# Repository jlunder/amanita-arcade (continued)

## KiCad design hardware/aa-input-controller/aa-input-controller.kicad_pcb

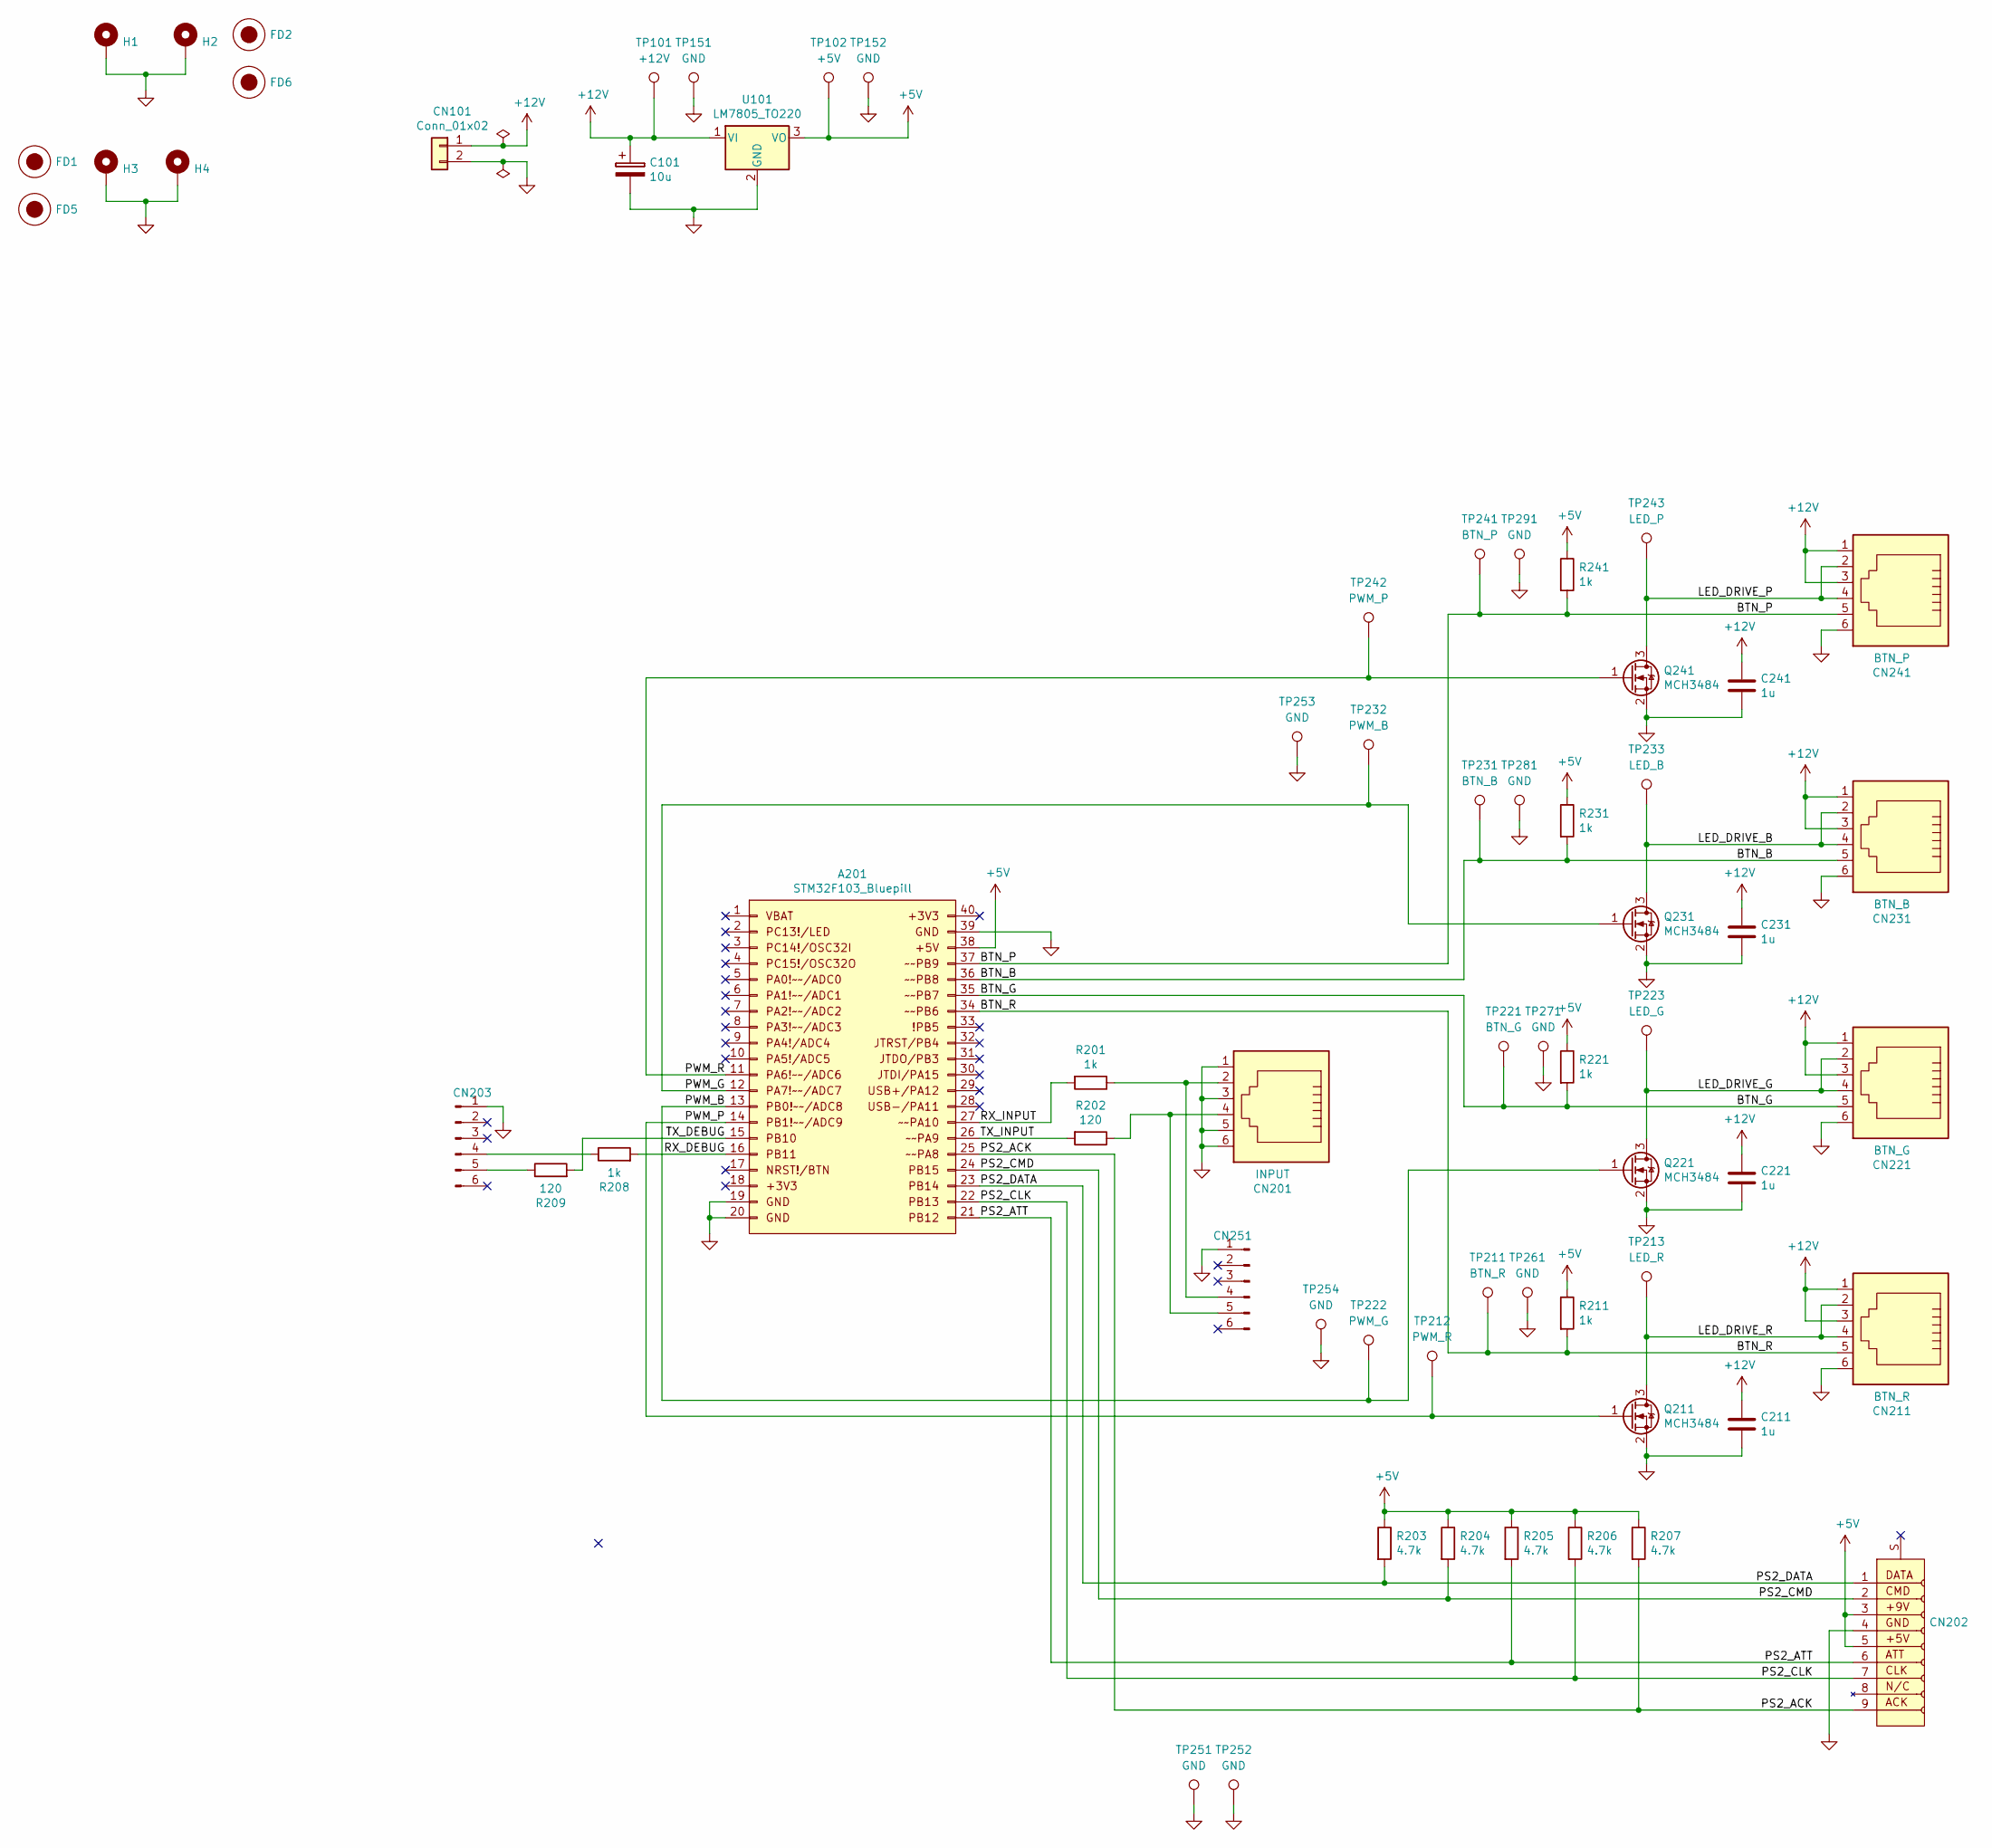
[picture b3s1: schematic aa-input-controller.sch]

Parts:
A201: STM32F103_Bluepill; Maple_Mini
C101: 10u; CP_Radial_D10.0mm_P2.50mm_P5.00mm
C211, C221, C231, C241: 1u; C_0805_2012Metric
CN101: Conn_01x02; SolderWirePad_1x02_P5.08mm_Drill1.5mm
CN201: INPUT; 6P6C_Assmann_A-2014-1-4
CN202: Connector_Sony_Playstation_DualShock_Female; Connector_SonyPS2DualShock_Female
CN203, CN251: Conn_01x06_Male; PinHeader_1x06_P2.54mm_Vertical
CN211: BTN_R; 6P6C_Assmann_A-2014-1-4
CN221: BTN_G; 6P6C_Assmann_A-2014-1-4
CN231: BTN_B; 6P6C_Assmann_A-2014-1-4
CN241: BTN_P; 6P6C_Assmann_A-2014-1-4
FD1, FD2: Fiducial; Fiducial_1mm_Dia_2.54mm_Outer_CopperTop
FD5, FD6: Fiducial; StencilAlignment_1.27mm
H1, H2, H3, H4: MountingHole_Pad; MountingHole_2.7mm_M2.5_Pad_Via
Q211, Q221, Q231, Q241: MCH3484; SOT-323_SC-70
R201, R208, R211, R221, R231, R241: 1k; R_0603_1608Metric
R202, R209: 120; R_0603_1608Metric
R203, R204, R205, R206, R207: 4.7k; R_0603_1608Metric
TP101: +12V; TestPoint_Loop_D1.80mm_Drill1.0mm_Beaded
TP102: +5V; TestPoint_Loop_D1.80mm_Drill1.0mm_Beaded
TP151, TP152, TP251, TP252, TP253, TP254, TP261, TP271, TP281, TP291: GND; TestPoint_Loop_D1.80mm_Drill1.0mm_Beaded
TP211: BTN_R; TestPoint_Loop_D1.80mm_Drill1.0mm_Beaded
TP212: PWM_R; TestPoint_Loop_D1.80mm_Drill1.0mm_Beaded
TP213: LED_R; TestPoint_Loop_D1.80mm_Drill1.0mm_Beaded
TP221: BTN_G; TestPoint_Loop_D1.80mm_Drill1.0mm_Beaded
TP222: PWM_G; TestPoint_Loop_D1.80mm_Drill1.0mm_Beaded
TP223: LED_G; TestPoint_Loop_D1.80mm_Drill1.0mm_Beaded
TP231: BTN_B; TestPoint_Loop_D1.80mm_Drill1.0mm_Beaded
TP232: PWM_B; TestPoint_Loop_D1.80mm_Drill1.0mm_Beaded
TP233: LED_B; TestPoint_Loop_D1.80mm_Drill1.0mm_Beaded
TP241: BTN_P; TestPoint_Loop_D1.80mm_Drill1.0mm_Beaded
TP242: PWM_P; TestPoint_Loop_D1.80mm_Drill1.0mm_Beaded
TP243: LED_P; TestPoint_Loop_D1.80mm_Drill1.0mm_Beaded
U101: LM7805_TO220; TO-220-3_Horizontal_TabDown

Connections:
+5V: A201.38, CN202.3, CN202.5, R203.1, R204.1, R205.1, R206.1, R207.1, R211.1, R221.1, R231.1, R241.1, TP102.1, U101.3 (VO)
+12V: C101.1, C211.1, C221.1, C231.1, C241.1, CN101.1, CN211.1, CN211.3, CN221.1, CN221.3, CN231.1, CN231.3, CN241.1, CN241.3, TP101.1, U101.1 (VI)
/BTN_B: A201.36, CN231.5, R231.2, TP231.1
/BTN_G: A201.35, CN221.5, R221.2, TP221.1
/BTN_P: A201.37, CN241.5, R241.2, TP241.1
/BTN_R: A201.34, CN211.5, R211.2, TP211.1
/LED_DRIVE_B: CN231.2, CN231.4, Q231.3 (D), TP233.1
/LED_DRIVE_G: CN221.2, CN221.4, Q221.3 (D), TP223.1
/LED_DRIVE_P: CN241.2, CN241.4, Q241.3 (D), TP243.1
/LED_DRIVE_R: CN211.2, CN211.4, Q211.3 (D), TP213.1
/PS2_ACK: A201.25, CN202.9, R207.2
/PS2_ATT: A201.21, CN202.6, R205.2
/PS2_CLK: A201.22, CN202.7, R206.2
/PS2_CMD: A201.24, CN202.2, R204.2
/PS2_DATA: A201.23, CN202.1, R203.2
/PWM_B: A201.13, Q221.1 (G), TP222.1
/PWM_G: A201.12, Q231.1 (G), TP232.1
/PWM_P: A201.14, Q211.1 (G), TP212.1
/PWM_R: A201.11, Q241.1 (G), TP242.1
/RX_DEBUG: A201.16, R208.2
/RX_INPUT: A201.27, R201.2
/TX_DEBUG: A201.15, R209.2
/TX_INPUT: A201.26, R202.2
GND: A201.19, A201.20, A201.39, C101.2, C211.2, C221.2, C231.2, C241.2, CN101.2, CN201.1, CN201.3, CN201.5, CN201.6, CN202.4, CN203.1, CN211.6, CN221.6, CN231.6, CN241.6, CN251.1, H1.1, H2.1, H3.1, H4.1, Q211.2 (S), Q221.2 (S), Q231.2 (S), Q241.2 (S), TP151.1, TP152.1, TP251.1, TP252.1, TP253.1, TP254.1, TP261.1, TP271.1, TP281.1, TP291.1, U101.2 (GND)
unnamed: CN201.2, CN251.4, R201.1
unnamed: CN201.4, CN251.5, R202.1
unnamed: CN203.4, R208.1
unnamed: CN203.5, R209.1

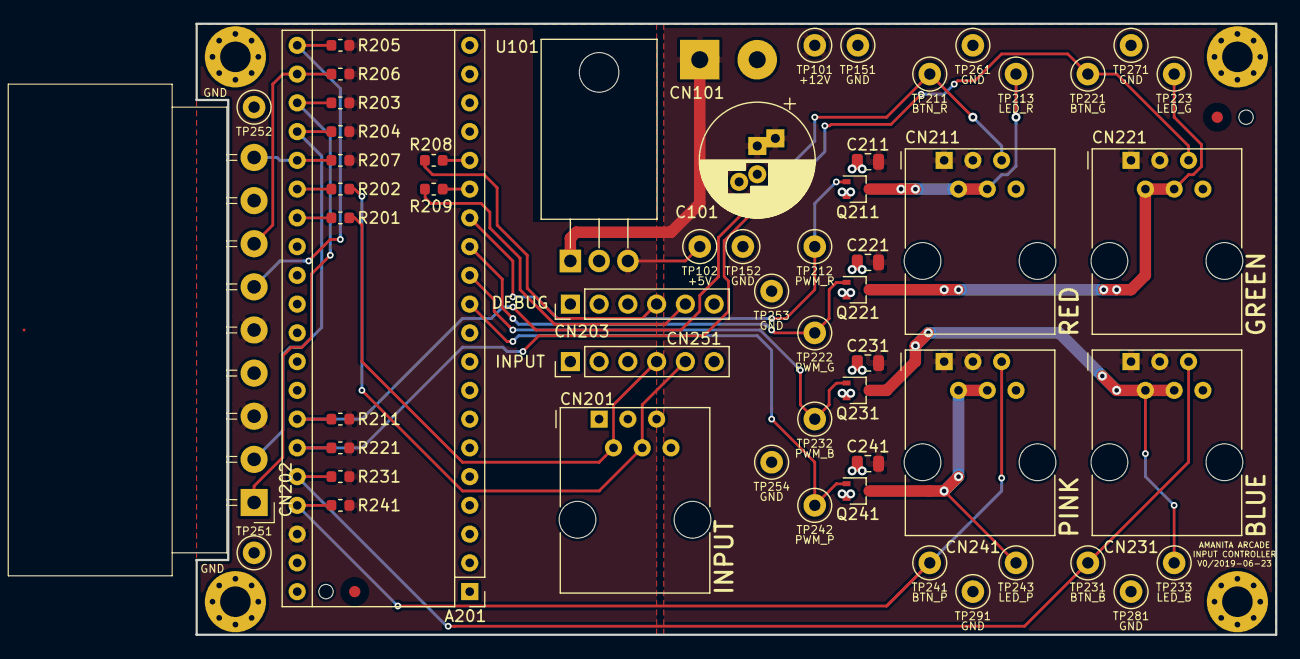
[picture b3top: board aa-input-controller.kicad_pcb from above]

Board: 2 copper layers, 95.4 x 54.0 mm, 65 parts (0 on the bottom side), 28 nets.

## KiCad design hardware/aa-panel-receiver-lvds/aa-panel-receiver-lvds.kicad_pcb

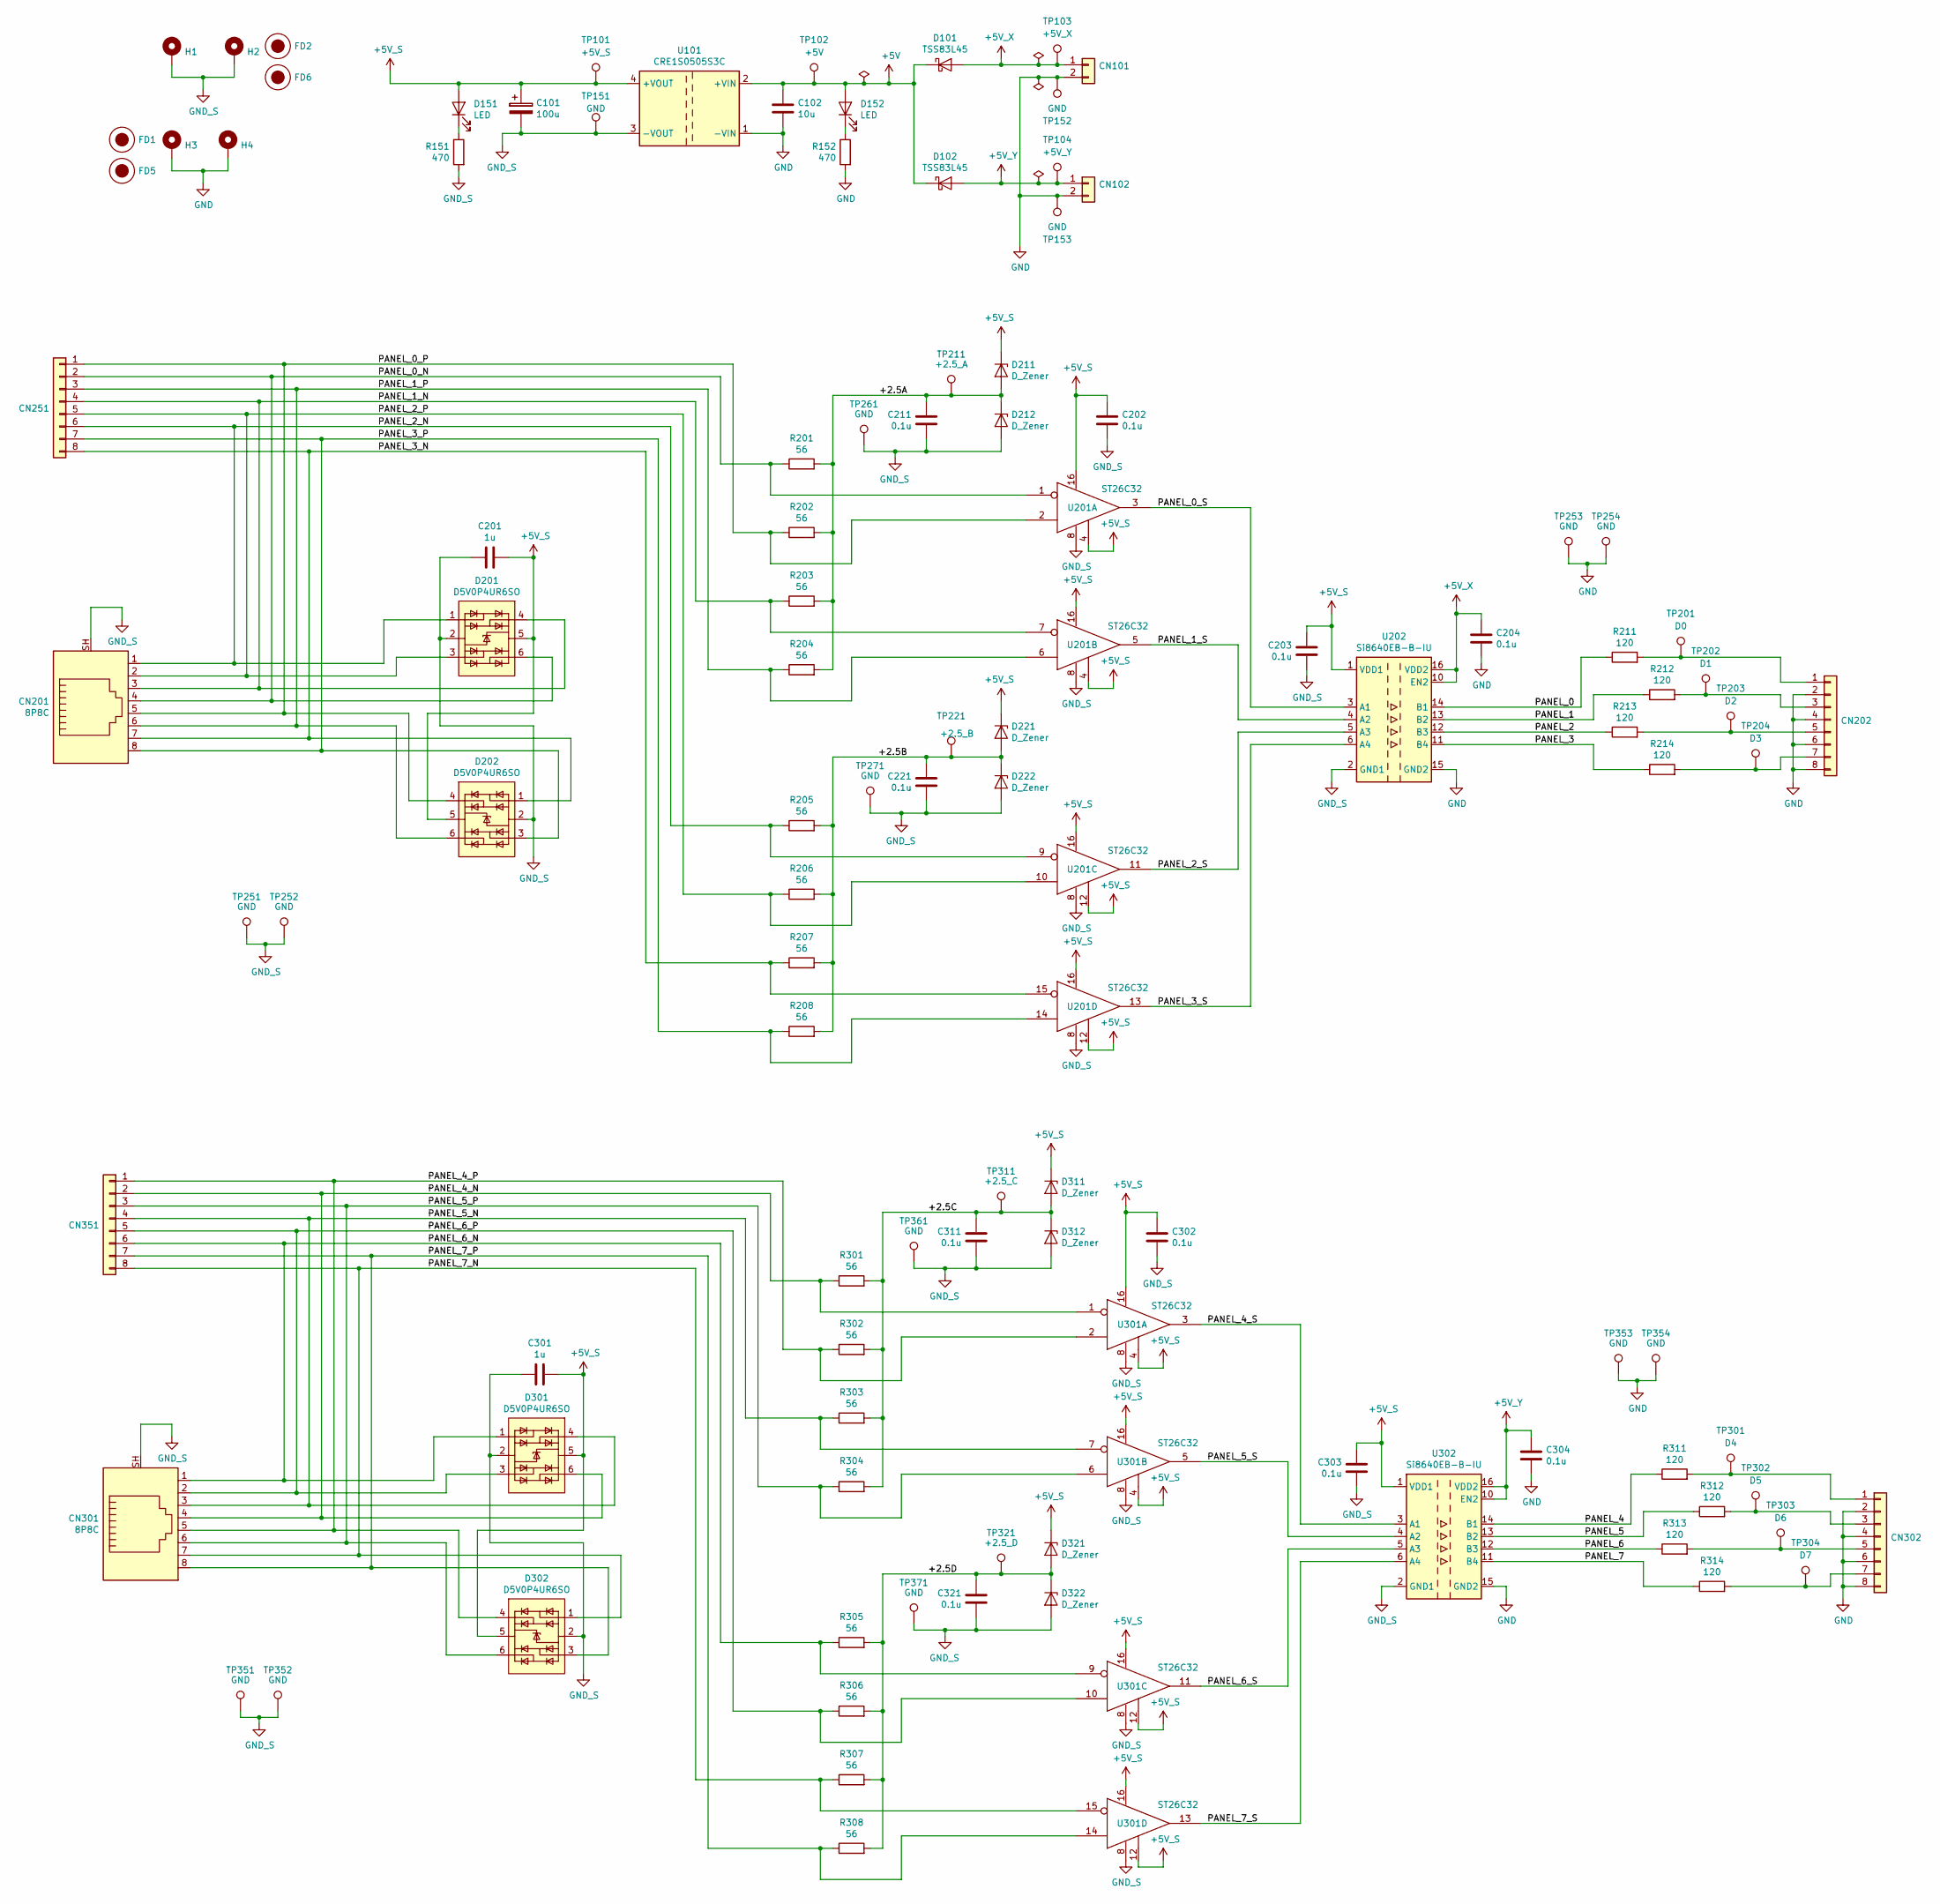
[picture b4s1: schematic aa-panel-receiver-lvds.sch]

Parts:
C101: 100u; CP_Radial_D10.0mm_P2.50mm_P5.00mm
C102: 10u; CP_Radial_D6.3mm_P2.50mm
C201, C301: 1u; C_0805_2012Metric
C202, C203, C204, C211, C221, C302, C303, C304, C311, C321: 0.1u; C_0603_1608Metric
CN101, CN102: Conn_01x02; SolderWirePad_1x02_P5.08mm_Drill1.5mm
CN201, CN301: 8P8C; 8P8C_Assmann_A-2014-2S-4
CN202, CN251, CN302, CN351: Conn_01x08; PinHeader_2x04_P2.54mm_Vertical
D101, D102: TSS83L45; D_SOD-128
D151, D152: LED; LED_0603_1608Metric
D201, D202, D301, D302: D5V0P4UR6SO; SOT-23-6
D211, D212, D221, D222, D311, D312, D321, D322: D_Zener; D_DO-35_SOD27_P2.54mm_Vertical_KathodeUp
FD1, FD2: Fiducial; Fiducial_1mm_Dia_2.54mm_Outer_CopperTop
FD5, FD6: Fiducial; StencilAlignment_1.27mm
H1, H2, H3, H4: MountingHole_Pad; MountingHole_2.7mm_M2.5_Pad_Via
R151, R152: 470; R_0603_1608Metric
R201, R202, R203, R204, R205, R206, R207, R208, R301, R302, R303, R304, R305, R306, R307, R308: 56; R_0603_1608Metric
R211, R212, R213, R214, R311, R312, R313, R314: 120; R_0603_1608Metric
TP101: +5V_S; TestPoint_Loop_D1.80mm_Drill1.0mm_Beaded
TP102: +5V; TestPoint_Loop_D1.80mm_Drill1.0mm_Beaded
TP103: +5V_X; TestPoint_Loop_D1.80mm_Drill1.0mm_Beaded
TP104: +5V_Y; TestPoint_Loop_D1.80mm_Drill1.0mm_Beaded
TP151, TP152, TP153, TP251, TP252, TP253, TP254, TP261, TP271, TP351, TP352, TP353, TP354, TP361, TP371: GND; TestPoint_Loop_D1.80mm_Drill1.0mm_Beaded
TP201: D0; TestPoint_Loop_D1.80mm_Drill1.0mm_Beaded
TP202: D1; TestPoint_Loop_D1.80mm_Drill1.0mm_Beaded
TP203: D2; TestPoint_Loop_D1.80mm_Drill1.0mm_Beaded
TP204: D3; TestPoint_Loop_D1.80mm_Drill1.0mm_Beaded
TP211: +2.5_A; TestPoint_Loop_D1.80mm_Drill1.0mm_Beaded
TP221: +2.5_B; TestPoint_Loop_D1.80mm_Drill1.0mm_Beaded
TP301: D4; TestPoint_Loop_D1.80mm_Drill1.0mm_Beaded
TP302: D5; TestPoint_Loop_D1.80mm_Drill1.0mm_Beaded
TP303: D6; TestPoint_Loop_D1.80mm_Drill1.0mm_Beaded
TP304: D7; TestPoint_Loop_D1.80mm_Drill1.0mm_Beaded
TP311: +2.5_C; TestPoint_Loop_D1.80mm_Drill1.0mm_Beaded
TP321: +2.5_D; TestPoint_Loop_D1.80mm_Drill1.0mm_Beaded
U101: CRE1S0505S3C; Converter_DCDC_muRata_CRE1xxxxxx3C_THT
U201, U301: ST26C32; SOIC-16_3.9x9.9mm_P1.27mm
U202, U302: Si8640EB-B-IU; QSOP-16_3.9x4.9mm_P0.635mm

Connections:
+5V: C102.1, D101.1 (K), D102.1 (K), D152.2 (A), TP102.1, U101.2 (+VIN)
+5V_S: C101.1, C201.1, C202.1, C203.1, C301.1, C302.1, C303.1, D151.2 (A), D201.5 (K), D202.5 (K), D211.1 (K), D221.1 (K), D301.5 (K), D302.5 (K), D311.1 (K), D321.1 (K), TP101.1, U101.4 (+VOUT), U201.4 (ENABLE), U201.12 (ENABLE), U201.16 (VCC), U202.1 (VDD1), U301.4 (ENABLE), U301.12 (ENABLE), U301.16 (VCC), U302.1 (VDD1)
+5V_X: C204.1, CN101.1, D101.2 (A), TP103.1, U202.10 (EN2), U202.16 (VDD2)
+5V_Y: C304.1, CN102.1, D102.2 (A), TP104.1, U302.10 (EN2), U302.16 (VDD2)
/+2.5A: C211.1, D211.2 (A), D212.1 (K), R201.2, R202.2, R203.2, R204.2, TP211.1
/+2.5B: C221.1, D221.2 (A), D222.1 (K), R205.2, R206.2, R207.2, R208.2, TP221.1
/+2.5C: C311.1, D311.2 (A), D312.1 (K), R301.2, R302.2, R303.2, R304.2, TP311.1
/+2.5D: C321.1, D321.2 (A), D322.1 (K), R305.2, R306.2, R307.2, R308.2, TP321.1
/PANEL_0: R211.1, U202.14 (B1)
/PANEL_0_N: CN201.4, CN251.2, D201.6 (K), R201.1, U201.1 (E-)
/PANEL_0_P: CN201.5, CN251.1, D202.4 (K), R202.1, U201.2 (E+)
/PANEL_0_S: U201.3 (OUT), U202.3 (A1)
/PANEL_1: R212.1, U202.13 (B2)
/PANEL_1_N: CN201.3, CN251.4, D201.4 (K), R203.1, U201.7 (E-)
/PANEL_1_P: CN201.6, CN251.3, D202.6 (K), R204.1, U201.6 (E+)
/PANEL_1_S: U201.5 (OUT), U202.4 (A2)
/PANEL_2: R213.1, U202.12 (B3)
/PANEL_2_N: CN201.1, CN251.6, D201.1 (K), R205.1, U201.9 (E-)
/PANEL_2_P: CN201.2, CN251.5, D201.3 (K), R206.1, U201.10 (E+)
/PANEL_2_S: U201.11 (OUT), U202.5 (A3)
/PANEL_3: R214.1, U202.11 (B4)
/PANEL_3_N: CN201.7, CN251.8, D202.1 (K), R207.1, U201.15 (E-)
/PANEL_3_P: CN201.8, CN251.7, D202.3 (K), R208.1, U201.14 (E+)
/PANEL_3_S: U201.13 (OUT), U202.6 (A4)
/PANEL_4: R311.1, U302.14 (B1)
/PANEL_4_N: CN301.4, CN351.2, D301.6 (K), R301.1, U301.1 (E-)
/PANEL_4_P: CN301.5, CN351.1, D302.4 (K), R302.1, U301.2 (E+)
/PANEL_4_S: U301.3 (OUT), U302.3 (A1)
/PANEL_5: R312.1, U302.13 (B2)
/PANEL_5_N: CN301.3, CN351.4, D301.4 (K), R303.1, U301.7 (E-)
/PANEL_5_P: CN301.6, CN351.3, D302.6 (K), R304.1, U301.6 (E+)
/PANEL_5_S: U301.5 (OUT), U302.4 (A2)
/PANEL_6: R313.1, U302.12 (B3)
/PANEL_6_N: CN301.1, CN351.6, D301.1 (K), R305.1, U301.9 (E-)
/PANEL_6_P: CN301.2, CN351.5, D301.3 (K), R306.1, U301.10 (E+)
/PANEL_6_S: U301.11 (OUT), U302.5 (A3)
/PANEL_7: R314.1, U302.11 (B4)
/PANEL_7_N: CN301.7, CN351.8, D302.1 (K), R307.1, U301.15 (E-)
/PANEL_7_P: CN301.8, CN351.7, D302.3 (K), R308.1, U301.14 (E+)
/PANEL_7_S: U301.13 (OUT), U302.6 (A4)
GND: C102.2, C204.2, C304.2, CN101.2, CN102.2, CN202.2, CN202.4, CN202.6, CN202.8, CN302.2, CN302.4, CN302.6, CN302.8, H3.1, H4.1, R152.2, TP152.1, TP153.1, TP253.1, TP254.1, TP353.1, TP354.1, U101.1 (-VIN), U202.9 (GND2), U202.15 (GND2), U302.9 (GND2), U302.15 (GND2)
GND_S: C101.2, C201.2, C202.2, C203.2, C211.2, C221.2, C301.2, C302.2, C303.2, C311.2, C321.2, CN201.SH, CN301.SH, D201.2 (A), D202.2 (A), D212.2 (A), D222.2 (A), D301.2 (A), D302.2 (A), D312.2 (A), D322.2 (A), H1.1, H2.1, R151.2, TP151.1, TP251.1, TP252.1, TP261.1, TP271.1, TP351.1, TP352.1, TP361.1, TP371.1, U101.3 (-VOUT), U201.8 (GND), U202.2 (GND1), U202.8 (GND1), U301.8 (GND), U302.2 (GND1), U302.8 (GND1)
unnamed: CN202.1, R211.2, TP201.1
unnamed: CN202.3, R212.2, TP202.1
unnamed: CN202.5, R213.2, TP203.1
unnamed: CN202.7, R214.2, TP204.1
unnamed: CN302.1, R311.2, TP301.1
unnamed: CN302.3, R312.2, TP302.1
unnamed: CN302.5, R313.2, TP303.1
unnamed: CN302.7, R314.2, TP304.1
unnamed: D151.1 (K), R151.1
unnamed: D152.1 (K), R152.1

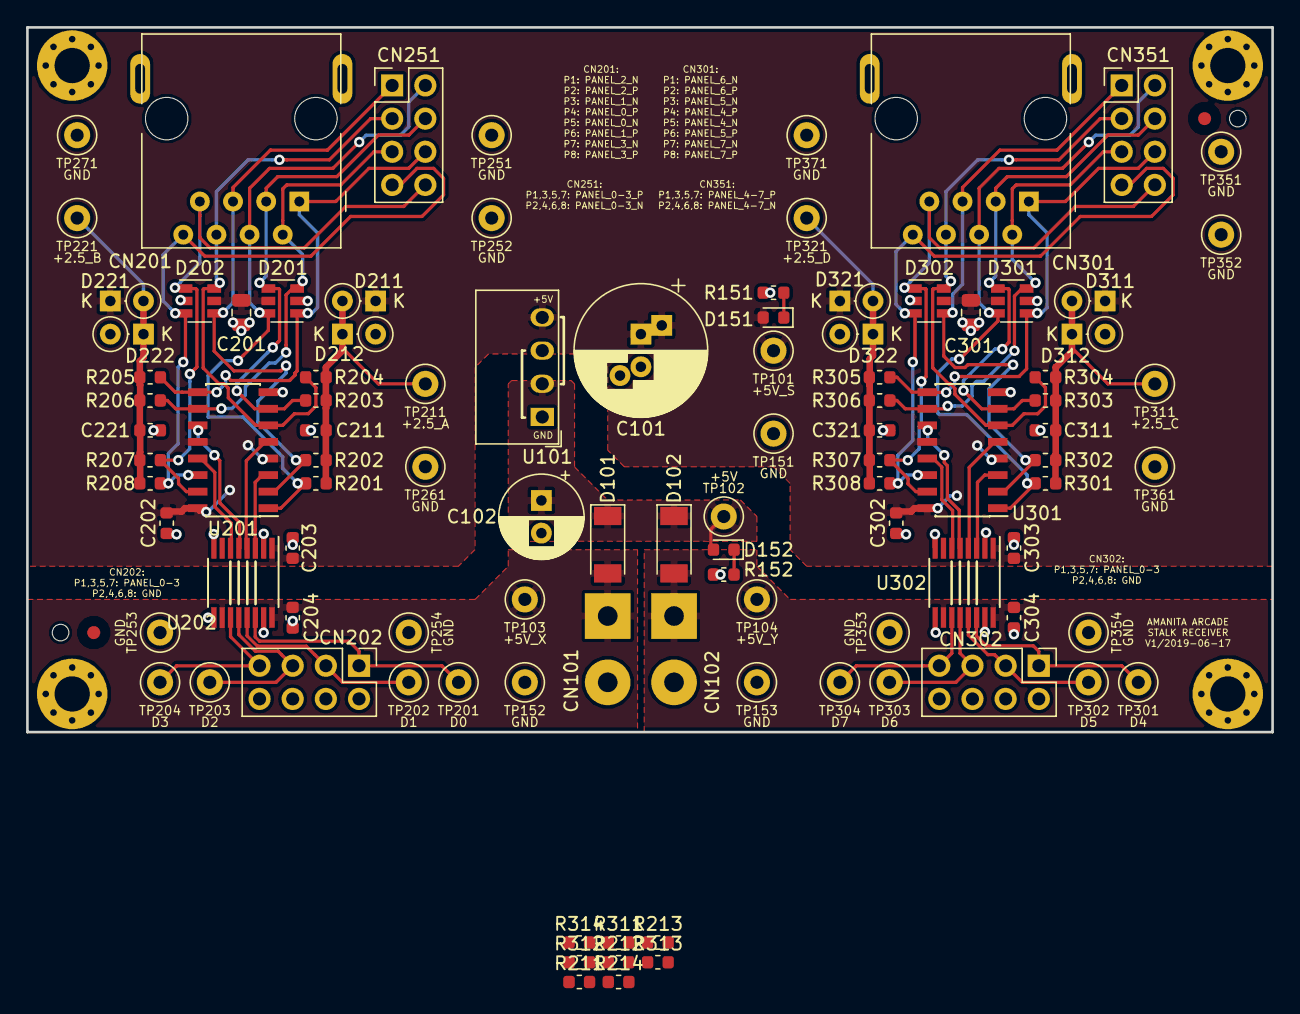
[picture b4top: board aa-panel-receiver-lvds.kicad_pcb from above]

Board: 2 copper layers, 95.4 x 54.0 mm, 108 parts (0 on the bottom side), 52 nets.

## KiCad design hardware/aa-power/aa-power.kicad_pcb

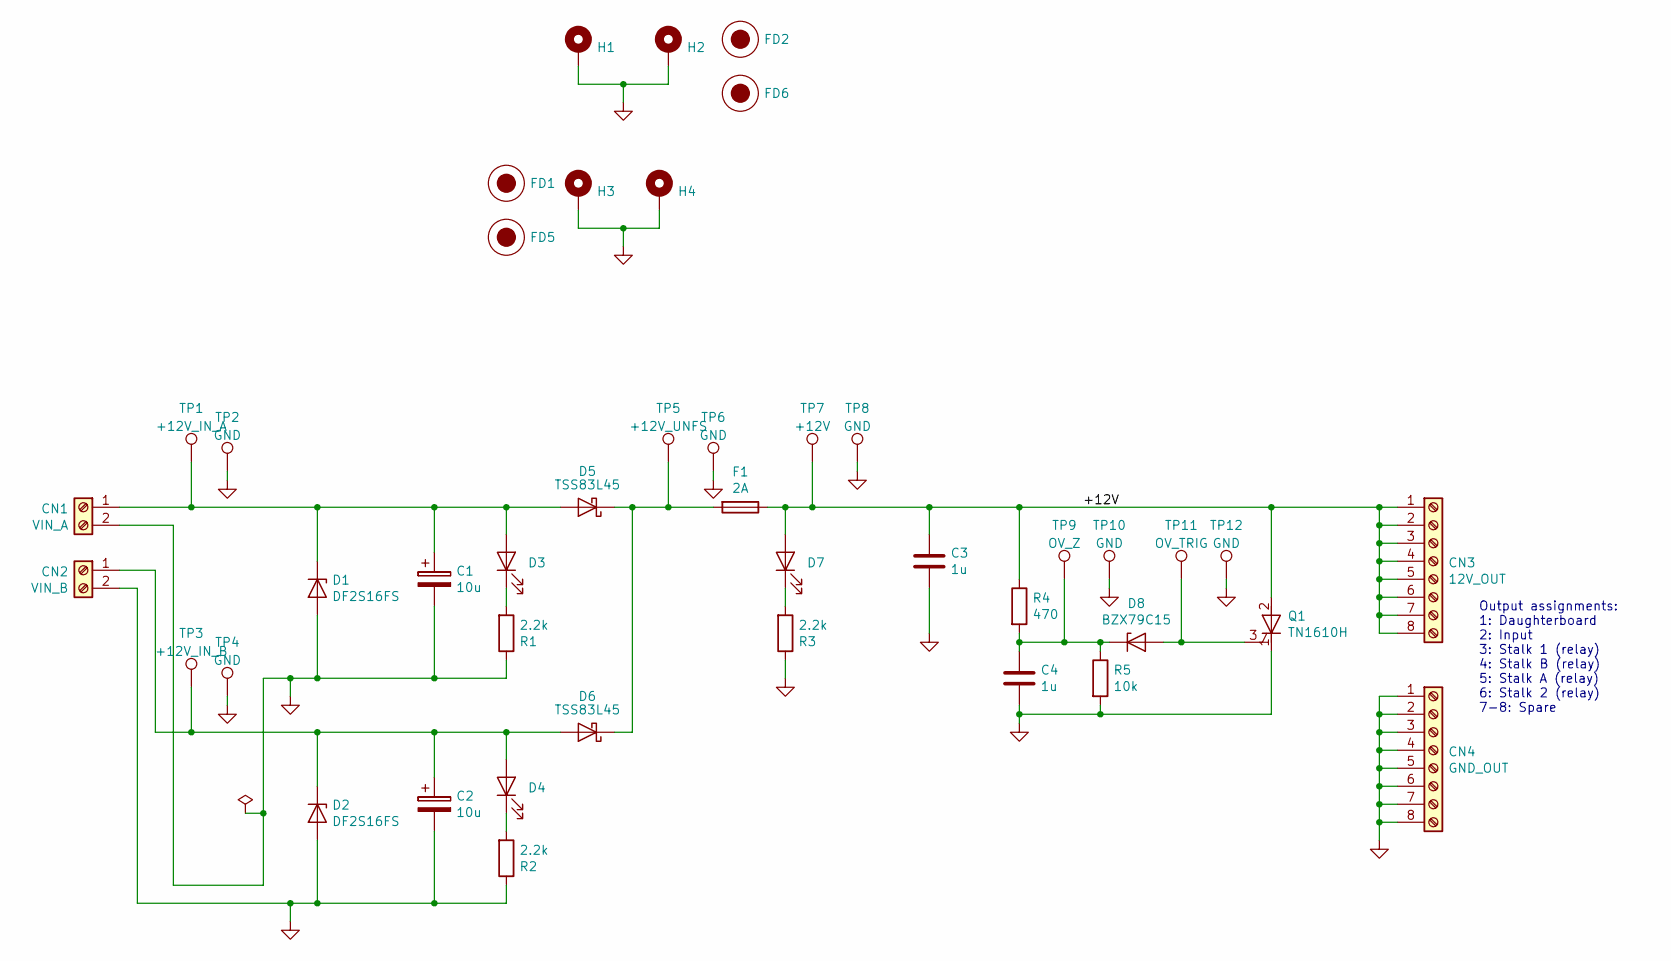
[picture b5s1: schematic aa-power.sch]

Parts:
C1, C2: 10u; CP_Radial_D5.0mm_P2.50mm
C3, C4: 1u; C_0805_2012Metric
CN1: VIN_A; SolderWirePad_1x02_P5.08mm_Drill1.5mm
CN2: VIN_B; SolderWirePad_1x02_P5.08mm_Drill1.5mm
CN3: 12V_OUT; TerminalBlock_OST_OSTYK44108030
CN4: GND_OUT; TerminalBlock_OST_OSTYK44108030
D1, D2: DF2S16FS; D_SOD-923
D3, D4, D7: LED; LED_0603_1608Metric
D5, D6: TSS83L45; D_SOD-128
D8: BZX79C15; D_DO-35_SOD27_P2.54mm_Vertical_KathodeUp
F1: 2A; Fuseholder_Clip_5x20_Bel_FC-211-22
FD1, FD2: Fiducial; Fiducial_1mm_Dia_2.54mm_Outer_CopperTop
FD5, FD6: Fiducial; StencilAlignment_1.27mm
H1, H2, H3, H4: MountingHole_Pad; MountingHole_2.7mm_M2.5_Pad_Via
Q1: TN1610H; TO-220-3_Horizontal_TabDown
R1, R2, R3: 2.2k; R_0603_1608Metric
R4: 470; R_0603_1608Metric
R5: 10k; R_0603_1608Metric
TP1: +12V_IN_A; TestPoint_Loop_D1.80mm_Drill1.0mm_Beaded
TP2, TP4, TP6, TP8, TP10, TP12: GND; TestPoint_Loop_D1.80mm_Drill1.0mm_Beaded
TP3: +12V_IN_B; TestPoint_Loop_D1.80mm_Drill1.0mm_Beaded
TP5: +12V_UNFS; TestPoint_Loop_D1.80mm_Drill1.0mm_Beaded
TP7: +12V; TestPoint_Loop_D1.80mm_Drill1.0mm_Beaded
TP9: OV_Z; TestPoint_Loop_D1.80mm_Drill1.0mm_Beaded
TP11: OV_TRIG; TestPoint_Loop_D1.80mm_Drill1.0mm_Beaded

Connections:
/+12V: C3.1, CN3.1, CN3.2, CN3.3, CN3.4, CN3.5, CN3.6, CN3.7, CN3.8, D7.2 (A), F1.1, Q1.2 (A), R4.1, TP7.1
GND: C1.2, C2.2, C3.2, C4.2, CN1.2, CN2.2, CN4.1, CN4.2, CN4.3, CN4.4, CN4.5, CN4.6, CN4.7, CN4.8, D1.2 (A), D2.2 (A), H1.1, H2.1, H3.1, H4.1, Q1.1 (K), R1.1, R2.1, R3.1, R5.2, TP2.1, TP4.1, TP6.1, TP8.1, TP10.1, TP12.1
unnamed: C1.1, CN1.1, D1.1 (K), D3.2 (A), D5.2 (A), TP1.1
unnamed: C2.1, CN2.1, D2.1 (K), D4.2 (A), D6.2 (A), TP3.1
unnamed: C4.1, D8.1 (K), R4.2, R5.1, TP9.1
unnamed: D3.1 (K), R1.2
unnamed: D4.1 (K), R2.2
unnamed: D5.1 (K), D6.1 (K), F1.2, TP5.1
unnamed: D7.1 (K), R3.2
unnamed: D8.2 (A), Q1.3 (G), TP11.1

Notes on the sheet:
Output assignments: 1: Daughterboard 2: Input 3: Stalk 1 (relay) 4: Stalk B (relay) 5: Stalk A (relay) 6: Stalk 2 (relay) 7-8: Spare

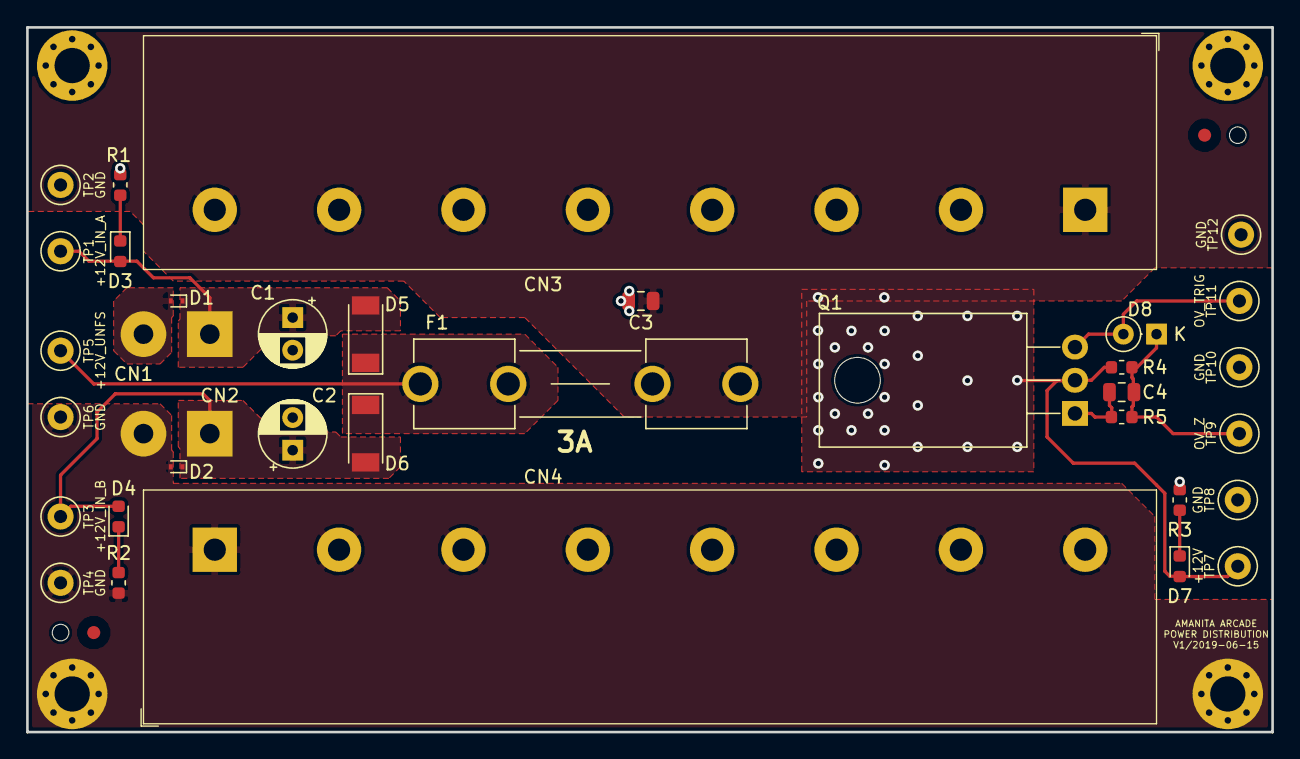
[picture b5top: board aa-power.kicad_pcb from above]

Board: 2 copper layers, 95.4 x 54.0 mm, 43 parts (0 on the bottom side), 10 nets.
